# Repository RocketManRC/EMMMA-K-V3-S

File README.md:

# EMMMA-K-V3-S
This is the code for the EMMMA-K-V3 slave processor (ESP32-S2 or ESP32-S3).

The main repository for the EMMMA-K-v3 along with an overall description of the project is here:

[https://github.com/RocketManRC/EMMMA-K-V3-M](https://github.com/RocketManRC/EMMMA-K-V3-M)

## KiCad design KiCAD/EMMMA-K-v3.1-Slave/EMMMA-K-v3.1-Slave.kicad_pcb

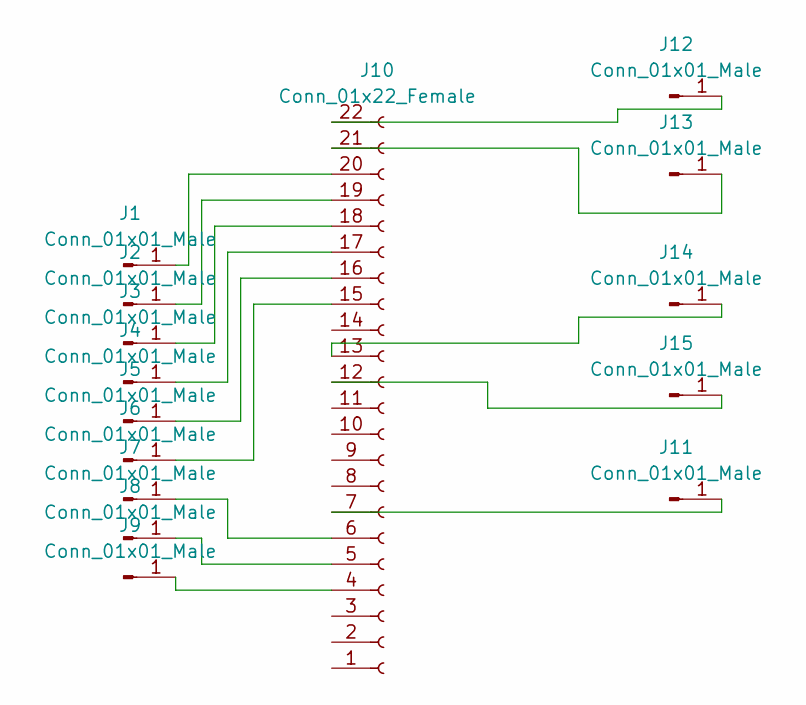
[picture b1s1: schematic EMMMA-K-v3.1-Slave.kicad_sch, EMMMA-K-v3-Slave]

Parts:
J1, J2, J3, J4, J5, J6, J7, J8, J9: Conn_01x01_Male; SolderWire-EMMMA-3mm1.7mm
J10: Conn_01x22_Female; PinHeader_1x22_P2.54mm_Vertical
J11, J12, J13, J14, J15: Conn_01x01_Male; SolderWire-1.5sqmm_1x01_D1.0mm_OD3mm

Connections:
unnamed: J1.1, J10.20
unnamed: J9.1, J10.4
unnamed: J8.1, J10.5
unnamed: J7.1, J10.6
unnamed: J10.7, J11.1
unnamed: J10.12, J15.1
unnamed: J10.13, J14.1
unnamed: J6.1, J10.15
unnamed: J5.1, J10.16
unnamed: J4.1, J10.17
unnamed: J3.1, J10.18
unnamed: J2.1, J10.19
unnamed: J10.21, J13.1
unnamed: J10.22, J12.1

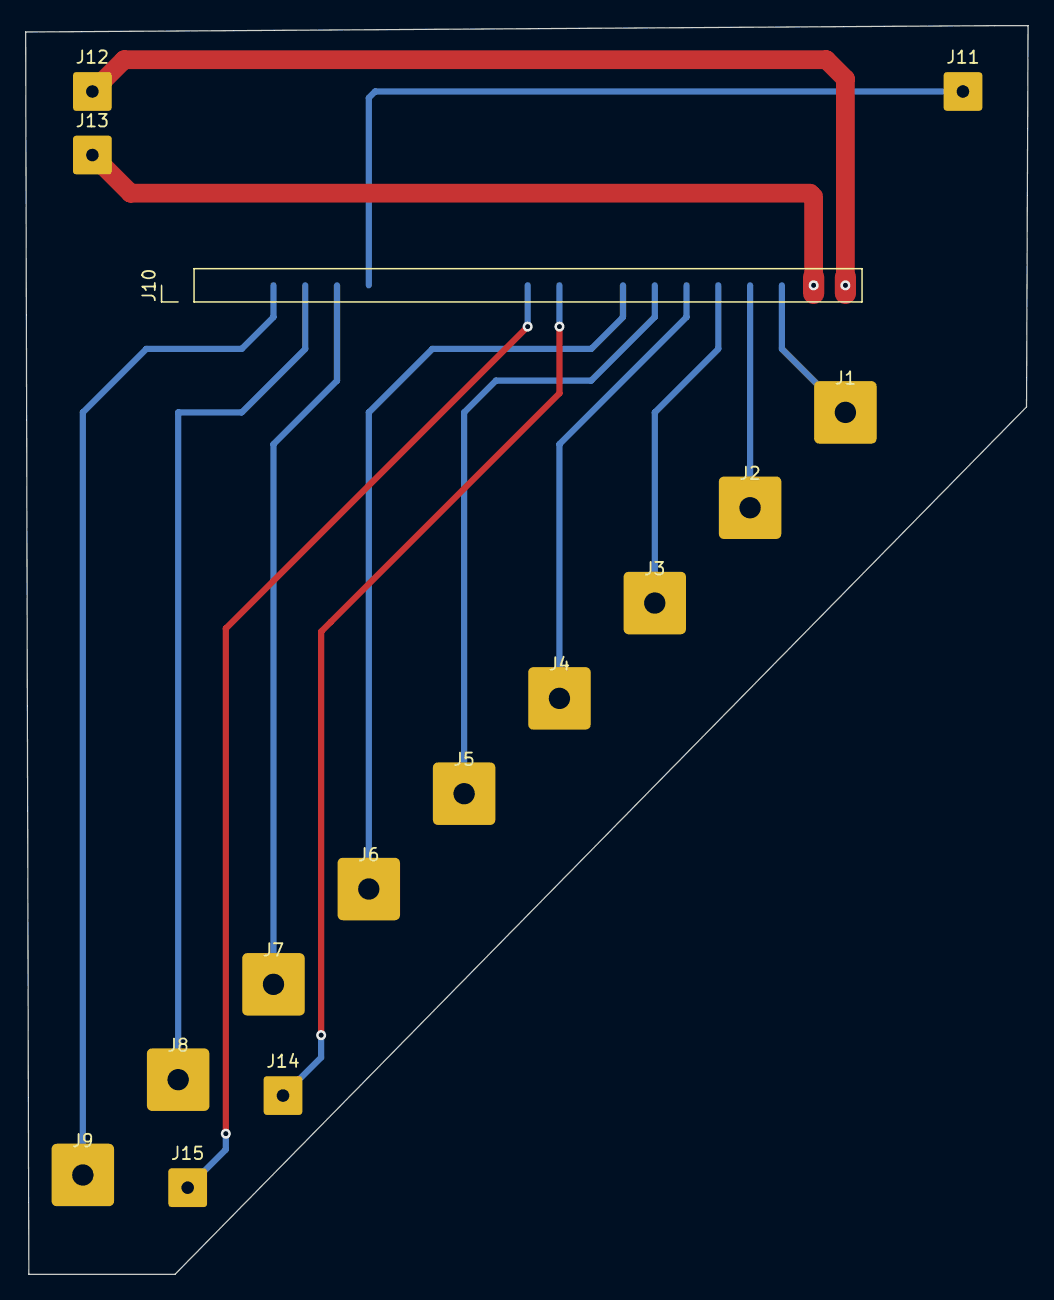
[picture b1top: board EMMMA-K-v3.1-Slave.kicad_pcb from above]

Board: 2 copper layers, 80.1 x 99.8 mm, 15 parts (0 on the bottom side), 14 nets.

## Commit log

2023-09-14 Add source and license files to Github repo
